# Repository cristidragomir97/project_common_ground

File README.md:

# Common Ground

Modular robot electronics built around a shared power and CAN backbone. Modules chain through XT30(2+2) connectors. Each module has a Seeed Studio XIAO RA4M1 for local control and is intended to communicate over a common CAN protocol.

## Shared architecture

- XT30(2+2) carries supply power, ground, CAN high, and CAN low.
- The XIAO RA4M1 and SN65HVD230 CAN transceiver provide local control and bus access.
- Boards include jumper-selectable 120 Ω CAN termination. Enable termination only at the two physical ends of a bus.

## Boards

| Board | Render | Role and hardware |
| --- | --- | --- |
| [mod_base](mod_base/) |  | - Battery input via XT60; charger/dock input via screw terminal<br>- Individually fused XT30(2+2) power/CAN outputs<br>- INA3221 monitors battery, dock, and load current<br>- UART and RS-485 interfaces |
| [mod_ddsm](mod_ddsm/) |  | - Four hub motor power outputs<br>- Four RS-485 and four UART connections, labelled FL/FR/BL/BR<br>- SP3485, TMUX1308 receive multiplexer, INA226 current monitor, and MOSFET power cutoff<br>- Two XT30(2+2) backbone connectors |
| [mod_feetech](mod_feetech/) |  | - Six three-pin Feetech servo connectors on a shared half-duplex data bus<br>- 8 A servo supply regulator (TPS56A37)<br>- Transmit/receive buffers, INA226 current monitor, and MOSFET power cutoff<br>- Two XT30(2+2) backbone connectors |
| [mod_sense](mod_sense/) |  | - LSM6DSOX six-axis IMU and MMC5983MA magnetometer over I²C<br>- Sensor interrupt signals<br>- Two XT30(2+2) backbone connectors |
| [mod_kitchensink](mod_kitchensink/mod_kitchensink/) |  | - Arduino-style power, digital/PWM, and analog headers<br>- Level shifters for compatibility with virtually every Arduino shield |
| [mod_raw](mod_raw/) | — | - Minimal starting point for custom modules<br>- Shared XIAO/CAN/power circuitry, INA226 current monitor, and MOSFET power cutoff |

## Example: XLeRobot module chain

The diagram shows one possible XLeRobot layout. The SBC receives power and connects to the control network through its own XT30(2+2) connection to the base board, then controls the robot modules. The Feetech boards locally drive their attached servos.

The base board provides six fused outputs, so these four modules use four separate outputs and leave two available. Each branch carries the same CAN bus, so connect only the two bus endpoints with termination enabled.

## Example: AMR with DDSM115 drive and RobStride arm

This AMR layout uses one mod_ddsm for four independently connected DDSM115 wheel motors, with the reBot Arm B601-DM and an IMU on separate base-board branches. The SBC connects through XT30(2+2) for power and control. The arm uses RobStride servos. Check the arm's connection and power requirements against its documentation before wiring.

The base outputs are drawn as separate branches for clarity. They remain electrically connected to the same power source and CAN network; the output fuses isolate branch faults, not CAN traffic. Check motor and arm peak currents against the battery, BMS, wiring, and branch fuse ratings.

## Repository

Each board directory contains KiCad project, schematic, and PCB layout files. Available board renders are shown above and collected in [renders](renders/).

This README describes the current hardware designs. A common CAN protocol is an intended system feature; firmware and a protocol specification are not currently included here.

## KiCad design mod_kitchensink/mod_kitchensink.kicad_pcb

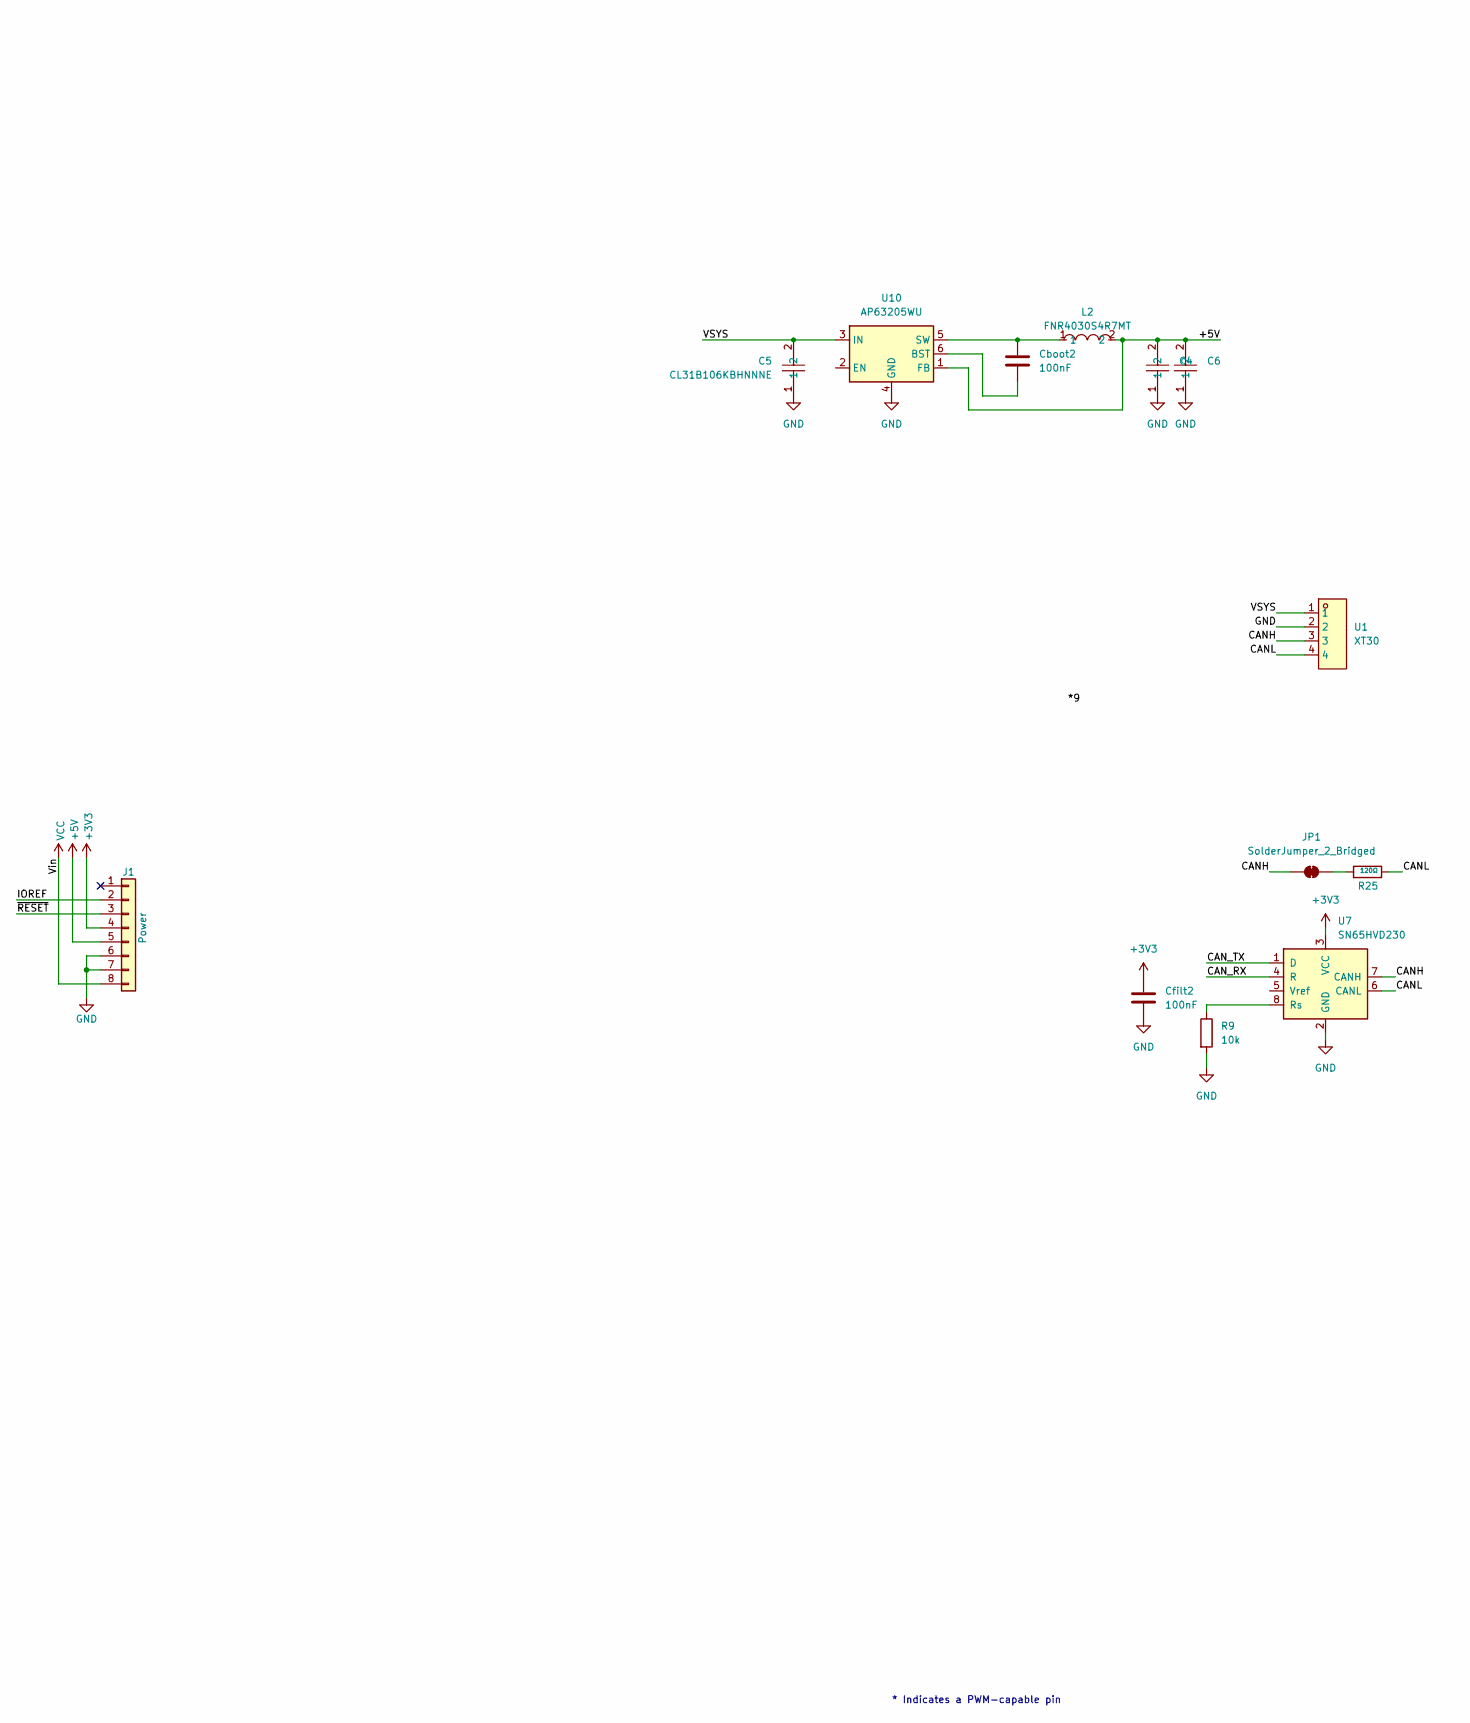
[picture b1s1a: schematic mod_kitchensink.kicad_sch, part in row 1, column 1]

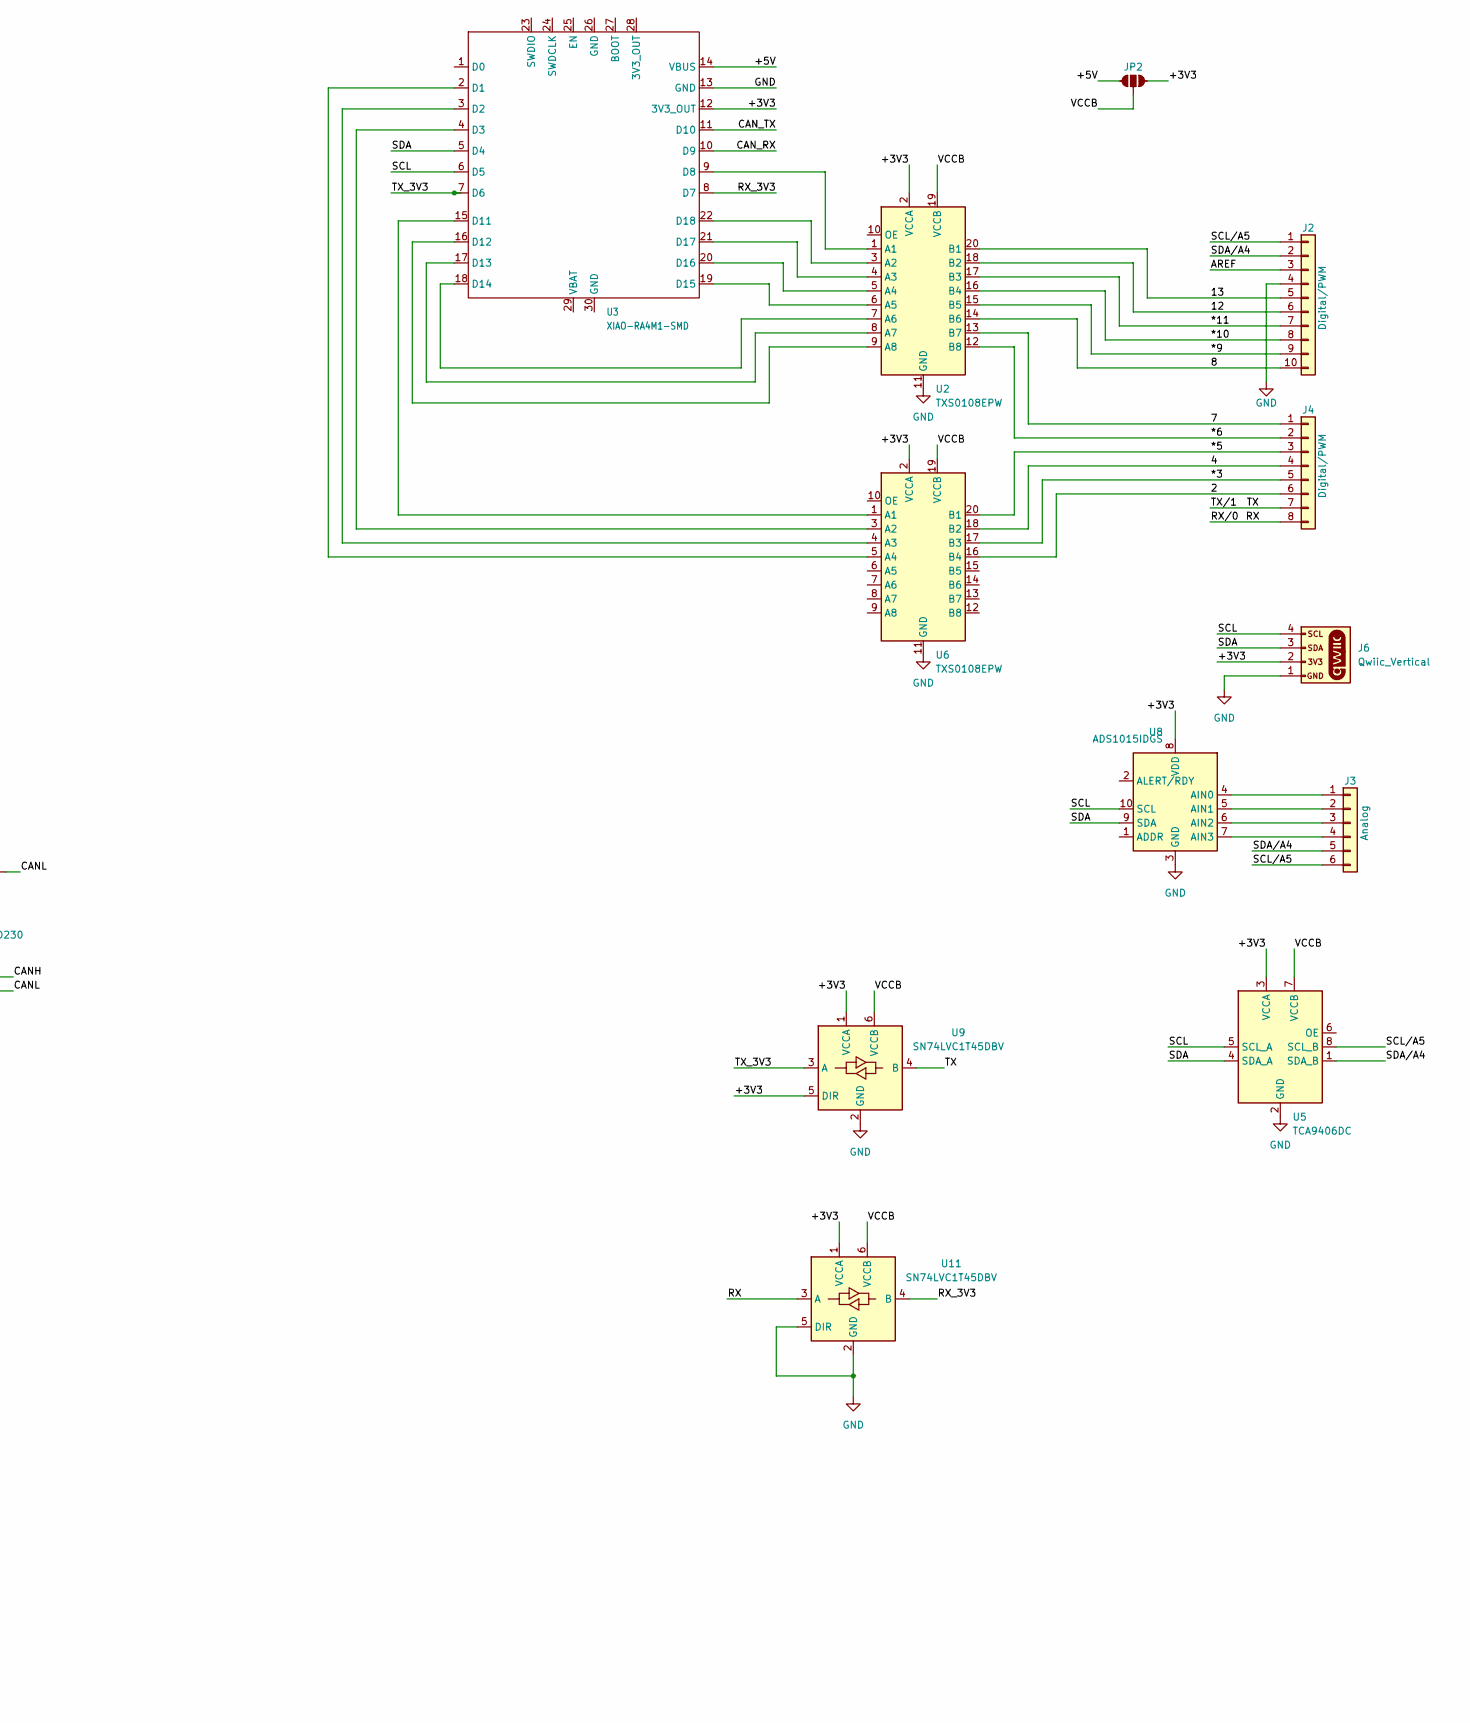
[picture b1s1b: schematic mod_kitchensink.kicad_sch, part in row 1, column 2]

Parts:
C4, C6: TCC0805X5R226M100FT; C0805; MPN TCC0805X5R226M100FT; LCSC Part C380338
C5: CL31B106KBHNNNE; C1206; MPN CL31B106KBHNNNE; LCSC Part C89632
Cboot2: 100nF; C_0603_1608Metric
Cfilt2: 100nF; C_0603_1608Metric
J1: Power; PinSocket_1x08_P2.54mm_Vertical
J2: Digital/PWM; PinSocket_1x10_P2.54mm_Vertical
J3: Analog; PinSocket_1x06_P2.54mm_Vertical
J4: Digital/PWM; PinSocket_1x08_P2.54mm_Vertical
J6: Qwiic_Vertical; JST_1x04_P1.0mm_Vertical_SMD
JP1: SolderJumper_2_Bridged; SolderJumper-2_P1.3mm_Bridged_Pad1.0x1.5mm
JP2: Jumper_3_NO_NoSilk
L2: FNR4030S4R7MT; IND-SMD_L4.0-W4.0_FNR40XXS; MPN FNR4030S4R7MT; LCSC Part C167874
R9: 10k; R_0402_1005Metric_Pad0.72x0.64mm_HandSolder
R25: 120Ω; R_0402_1005Metric; Overload Voltage (Max) 50V; Tolerance ±1%; Part 0402WGF1200TCE; LCSC C25079
U1: XT30; CONN-TH_4P-XT30PW-M; MPN XT30PW(2+2)-M.G.B; LCSC Part C19268030
U2, U6: TXS0108EPW; TSSOP-20_4.4x6.5mm_P0.65mm
U3: XIAO-RA4M1-SMD; XIAO-R4-SMD
U5: TCA9406DC
U7: SN65HVD230; SOIC-8_3.9x4.9mm_P1.27mm
U8: ADS1015IDGS; TSSOP-10_3x3mm_P0.5mm
U9, U11: SN74LVC1T45DBV; SOT-23-6
U10: AP63205WU; TSOT-23-6

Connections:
+3V3: Cfilt2.1, J1.4, J6.2, JP2.3 (C), U2.2 (VCCA), U3.12 (3V3_OUT), U5.3 (VCCA), U6.2 (VCCA), U7.3 (VCC), U8.8 (VDD), U9.1 (VCCA), U9.5 (DIR), U11.1 (VCCA)
+5V: C4.2, C6.2, J1.5, JP2.1 (A), L2.2, U3.14 (VBUS), U10.1 (FB)
/2: J4.6, U6.16 (B4)
/4: J4.4, U6.18 (B2)
/7: J4.1, U2.13 (B7)
/8: J2.10, U2.14 (B6)
/12: J2.6, U2.18 (B2)
/13: J2.5, U2.20 (B1)
/*3: J4.5, U6.17 (B3)
/*5: J4.3, U6.20 (B1)
/*6: J4.2, U2.12 (B8)
/*9: J2.9, U2.15 (B5)
/*10: J2.8, U2.16 (B4)
/*11: J2.7, U2.17 (B3)
/AREF: J2.3
/CANH: JP1.1 (A), U1.3, U7.7 (CANH)
/CANL: R25.2, U1.4, U7.6 (CANL)
/CAN_RX: U3.10 (D9), U7.4 (R)
/CAN_TX: U3.11 (D10), U7.1 (D)
/IOREF: J1.2
/RX: J4.8, U11.3 (A)
/RX_3V3: U3.8 (D7), U11.4 (B)
/SCL: J6.4, U3.6 (D5), U5.5 (SCL_A), U8.10 (SCL)
/SCL/A5: J2.1, J3.6, U5.8 (SCL_B)
/SDA: J6.3, U3.5 (D4), U5.4 (SDA_A), U8.9 (SDA)
/SDA/A4: J2.2, J3.5, U5.1 (SDA_B)
/TX: J4.7, U9.4 (B)
/TX_3V3: U3.7 (D6), U9.3 (A)
/VCCB: JP2.2 (B), U2.19 (VCCB), U5.7 (VCCB), U6.19 (VCCB), U9.6 (VCCB), U11.6 (VCCB)
/VSYS: C5.2, U1.1, U10.3 (IN)
/~RESET: J1.3
GND: C4.1, C5.1, C6.1, Cfilt2.2, J1.6, J1.7, J2.4, J6.1, R9.2, U1.2, U2.11 (GND), U3.13 (GND), U5.2 (GND), U6.11 (GND), U7.2 (GND), U8.3 (GND), U9.2 (GND), U10.4 (GND), U11.2 (GND), U11.5 (DIR)
unnamed: J3.1, U8.4 (AIN0)
unnamed: J3.2, U8.5 (AIN1)
unnamed: J3.3, U8.6 (AIN2)
unnamed: J3.4, U8.7 (AIN3)
unnamed: JP1.2 (B), R25.1
unnamed: U2.1 (A1), U3.9 (D8)
unnamed: U2.3 (A2), U3.22 (D18)
unnamed: U2.4 (A3), U3.21 (D17)
unnamed: U2.5 (A4), U3.20 (D16)
unnamed: U2.6 (A5), U3.19 (D15)
unnamed: U2.7 (A6), U3.18 (D14)
unnamed: U2.8 (A7), U3.17 (D13)
unnamed: U2.9 (A8), U3.16 (D12)
unnamed: U3.2 (D1), U6.5 (A4)
unnamed: U3.3 (D2), U6.4 (A3)
unnamed: U3.4 (D3), U6.3 (A2)
unnamed: U3.15 (D11), U6.1 (A1)
unnamed: R9.1, U7.8 (Rs)
unnamed: Cboot2.2, U10.6 (BST)
unnamed: Cboot2.1, L2.1, U10.5 (SW)
VCC: J1.8

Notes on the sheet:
* Indicates a PWM-capable pin

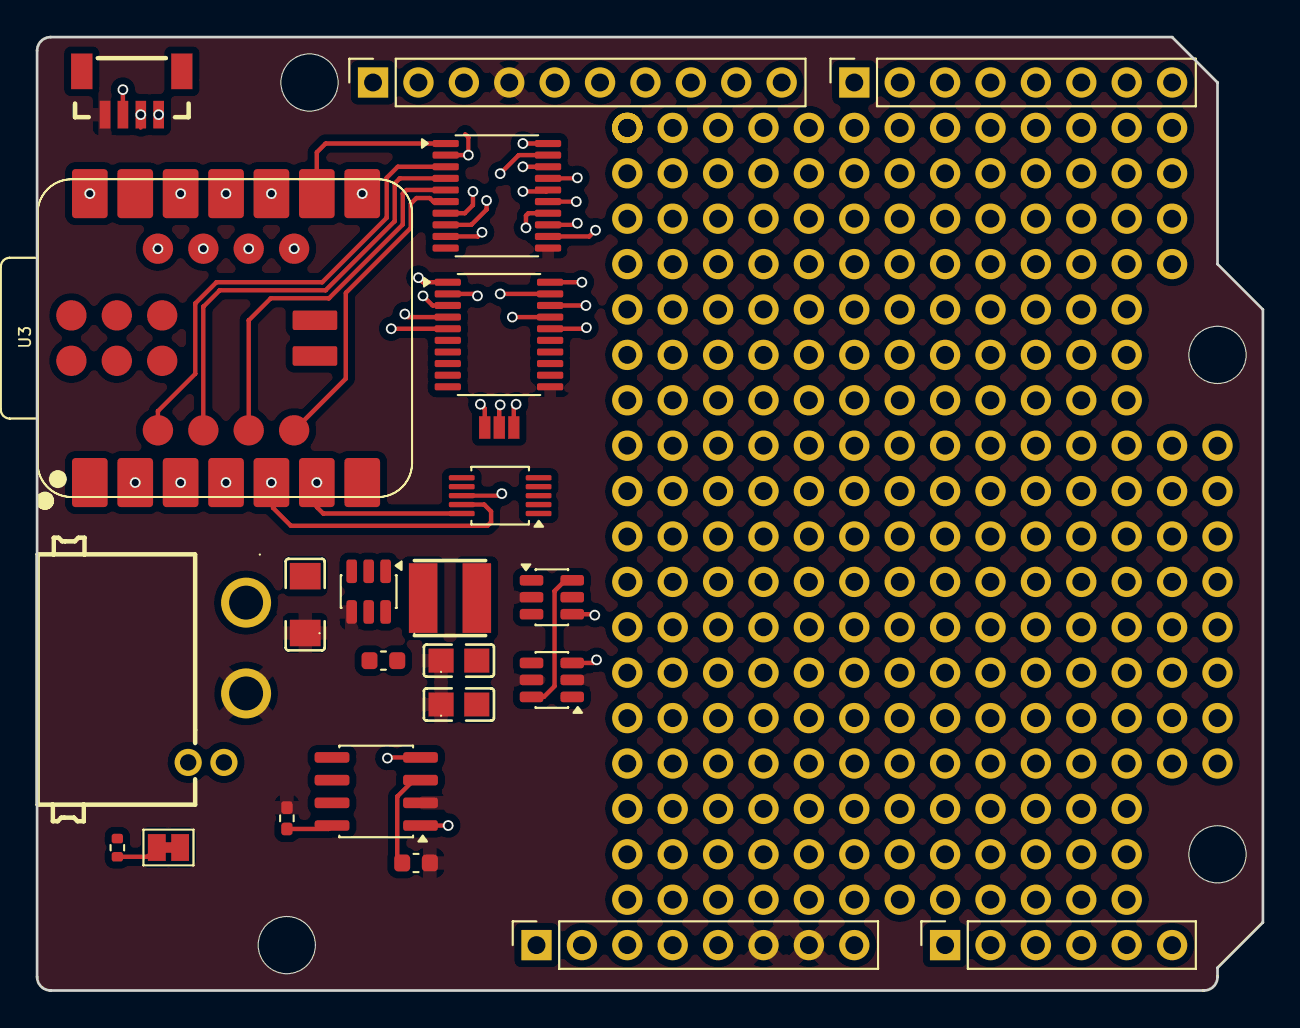
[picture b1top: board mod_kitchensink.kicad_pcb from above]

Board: 4 copper layers, 68.6 x 53.3 mm, 264 parts (0 on the bottom side), 49 nets.

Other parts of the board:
H6, H7, H8, H9, H10, H11, H12, H13, H14, H15, H16, H17, H18, H19, H20, H21, H22, H23, H24, H25, H26, H27, H28, H29, H30, H31, H32, H33, H34, H35, H36, H37, H38, H39, H40, H41, H42, H43, H44, H45, H46, H47, H48, H49, H50, H51, H52, H53, H54, H55, H56, H57, H58, H59, H60, H61, H62, H63, H64, H65, H66, H67, H68, H69, H74, H75, H76, H77, H78, H79, H80, H81, H82, H83, H84, H85, H90, H91, H92, H93, H94, H95, H96, H97, H98, H99, H100, H101, H106, H107, H108, H109, H110, H111, H112, H113, H114, H115, H116, H117, H118, H119, H124, H125, H126, H127, H128, H129, H130, H131, H132, H133, H134, H135, H136, H137, H140, H141, H142, H143, H144, H145, H146, H147, H148, H149, H150, H151, H152, H153, H156, H157, H158, H159, H160, H161, H162, H163, H164, H165, H166, H167, H168, H169, H172, H173, H174, H175, H176, H177, H178, H179, H180, H181, H182, H183, H184, H185, H188, H189, H190, H191, H192, H193, H194, H195, H196, H197, H198, H199, H200, H201, H206, H207, H208, H209, H210, H211, H212, H213, H214, H215, H216, H217, H218, H219, H223, H224, H225, H226, H227, H228, H229, H230, H231, H232, H233, H234, H235, H236, H240, H241, H242, H243, H244, H245, H246, H247, H248, H249, H250, H251, H256, H257, H258, H259, H260, H261, H262, H263, H264, H265, H266, H267, H278, H279, H280, H281, H282, H283, H284, H285, H286, H287, H288, H289: Perf_1x01_Square
MH1, MH2, MH3, MH4: MountingHole_3.2mm

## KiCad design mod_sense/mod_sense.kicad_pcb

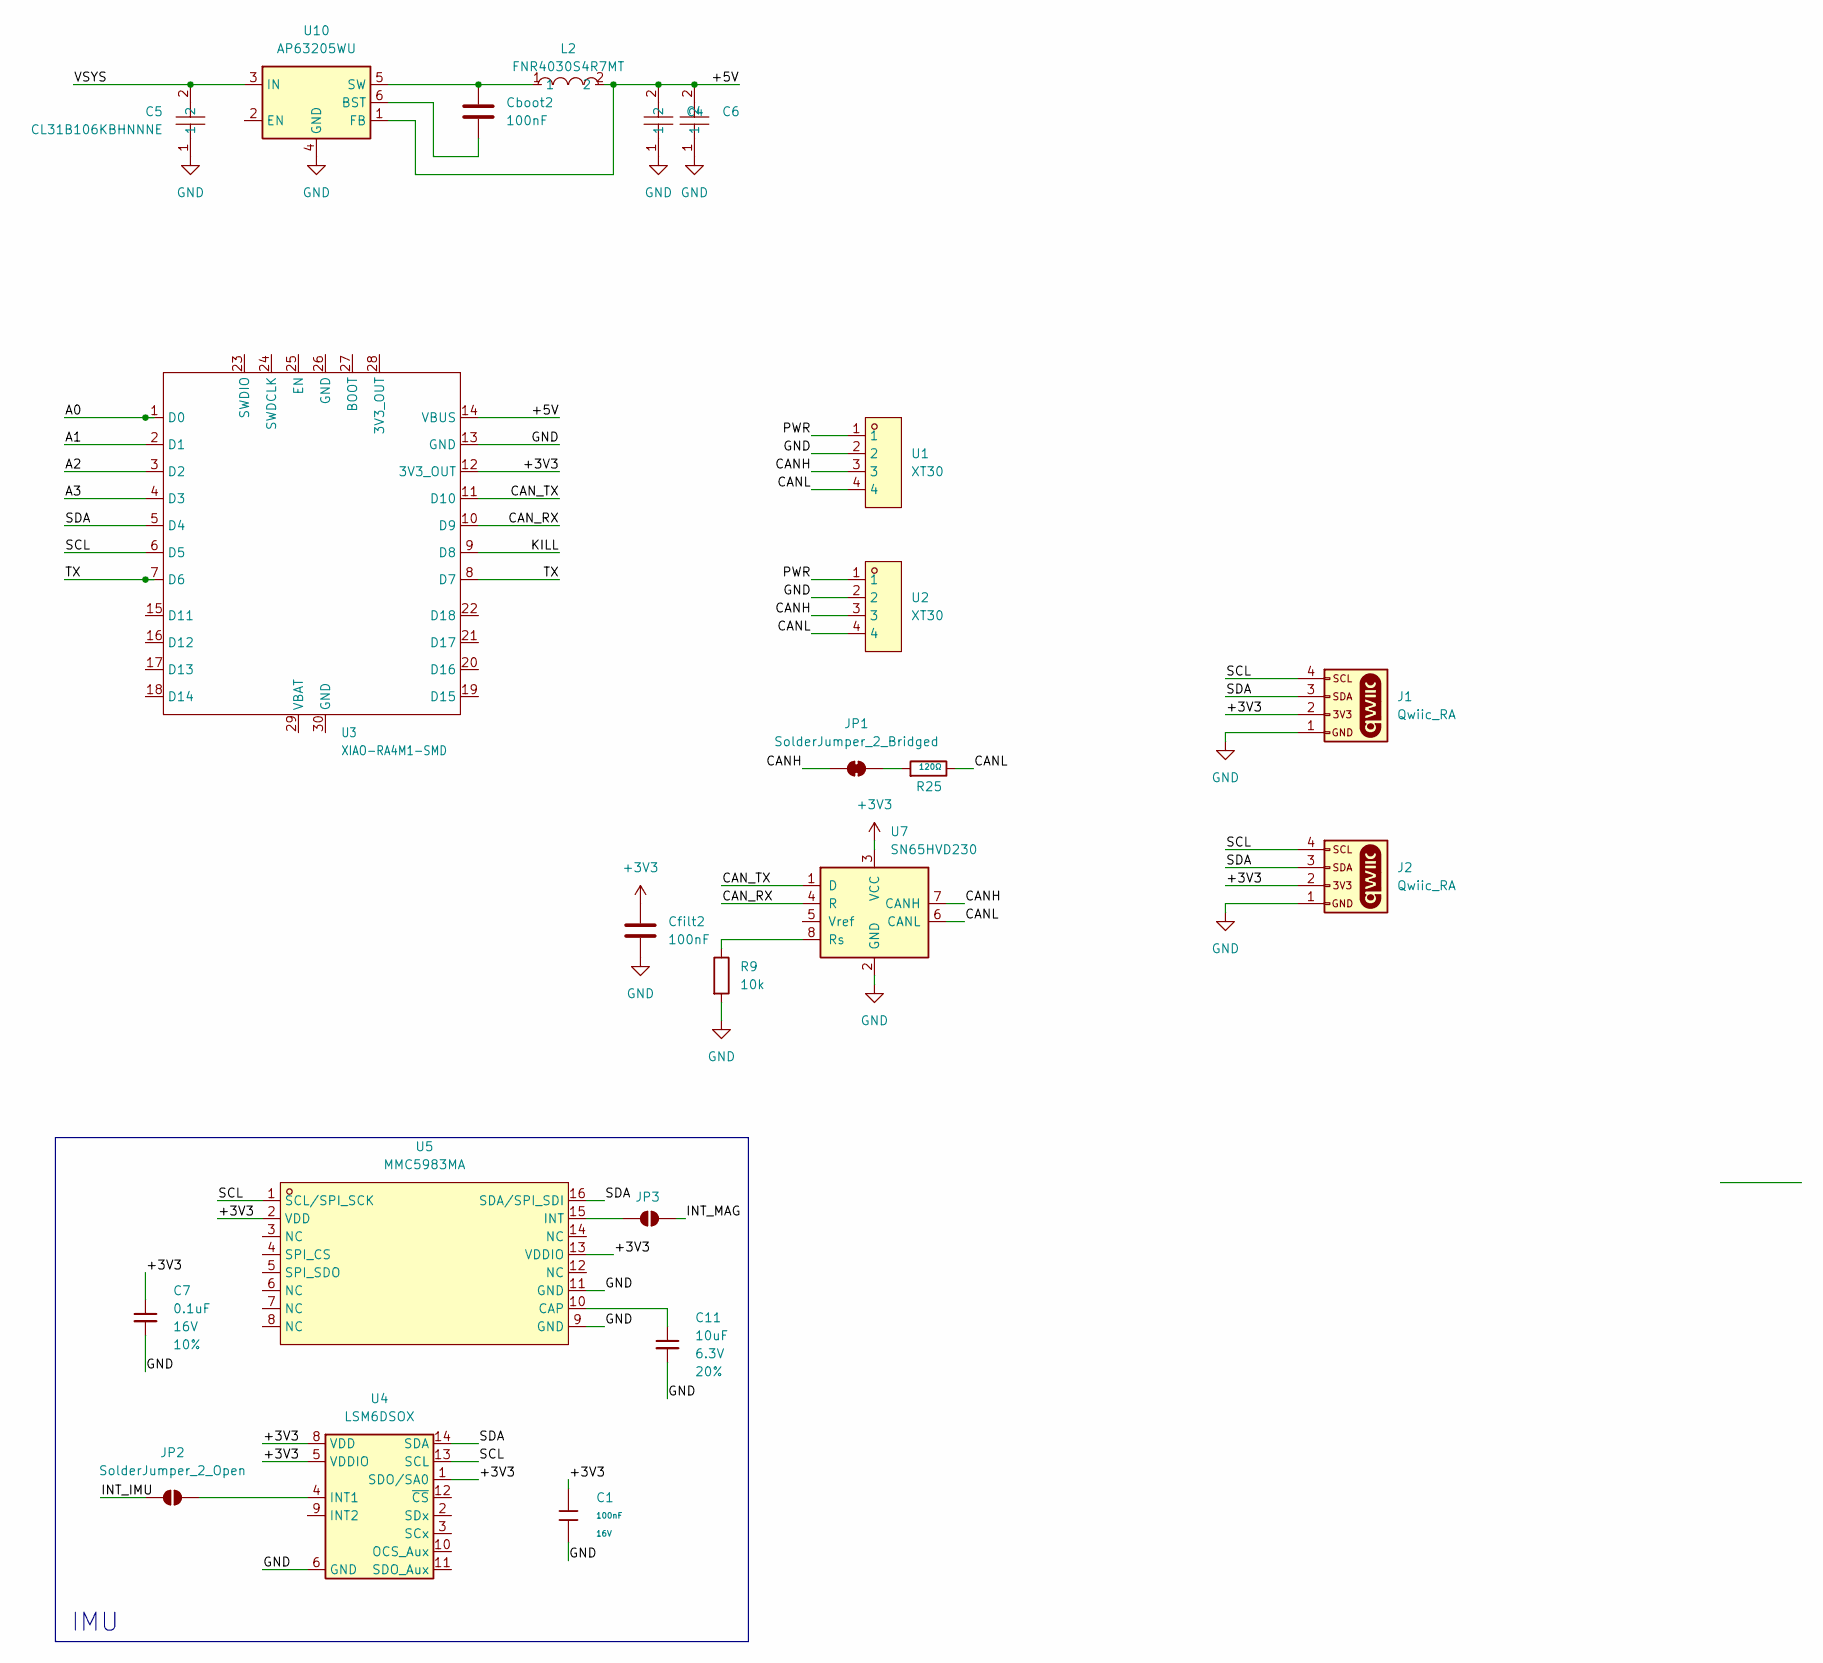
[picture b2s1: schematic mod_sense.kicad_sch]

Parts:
C1: 100nF; C_0402; Voltage Rated 16V; Tolerance ±10%; Part CL05B104KO5NNNC; LCSC C1525
C4, C6: TCC0805X5R226M100FT; C0805; MPN TCC0805X5R226M100FT; LCSC Part C380338
C5: CL31B106KBHNNNE; C1206; MPN CL31B106KBHNNNE; LCSC Part C89632
C7: 0.1uF; C_0402_1005Metric; Voltage 16V; Tolerance 10%
C11: 10uF; C_0402_1005Metric; Voltage 6.3V; Tolerance 20%
Cboot2: 100nF; C_0603_1608Metric
Cfilt2: 100nF; C_0603_1608Metric
J1, J2: Qwiic_RA; JST_1x04_P1.0mm_Horizontal_SMD
JP1: SolderJumper_2_Bridged; SolderJumper-2_P1.3mm_Bridged_Pad1.0x1.5mm
JP2, JP3: SolderJumper_2_Open; SolderJumper-2_P1.3mm_Open_RoundedPad1.0x1.5mm
L2: FNR4030S4R7MT; IND-SMD_L4.0-W4.0_FNR40XXS; MPN FNR4030S4R7MT; LCSC Part C167874
R9: 10k; R_0402_1005Metric_Pad0.72x0.64mm_HandSolder
R25: 120Ω; R_0402_1005Metric; Overload Voltage (Max) 50V; Tolerance ±1%; Part 0402WGF1200TCE; LCSC C25079
U1, U2: XT30; CONN-TH_4P-XT30PW-M; MPN XT30PW(2+2)-M.G.B; LCSC Part C19268030
U3: XIAO-RA4M1-SMD; XIAO-R4-SMD
U4: LSM6DSOX; ST_LGA-14L_2.5x3.0mm_P0.5mm_4x3
U5: MMC5983MA; LGA-16_L3.0-W3.0-P0.50-BL_SQ; LCSC Part C404329
U7: SN65HVD230; SOIC-8_3.9x4.9mm_P1.27mm
U10: AP63205WU; TSOT-23-6

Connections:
+3V3: C1.1, C7.1, Cfilt2.1, J1.2, J2.2, U3.12 (3V3_OUT), U4.1 (SDO/SA0), U4.5 (VDDIO), U4.8 (VDD), U5.2 (VDD), U5.13 (VDDIO), U7.3 (VCC)
/+5V: C4.2, C6.2, L2.2, U3.14 (VBUS), U10.1 (FB)
/A0: U3.1 (D0)
/A1: U3.2 (D1)
/A2: U3.3 (D2)
/A3: U3.4 (D3)
/CANH: JP1.1 (A), U1.3, U2.3, U7.7 (CANH)
/CANL: R25.2, U1.4, U2.4, U7.6 (CANL)
/CAN_RX: U3.10 (D9), U7.4 (R)
/CAN_TX: U3.11 (D10), U7.1 (D)
/INT_IMU: JP2.1 (A)
/INT_MAG: JP3.2 (B)
/KILL: U3.9 (D8)
/PWR: U1.1, U2.1
/SCL: J1.4, J2.4, U3.6 (D5), U4.13 (SCL), U5.1 (SCL/SPI_SCK)
/SDA: J1.3, J2.3, U3.5 (D4), U4.14 (SDA), U5.16 (SDA/SPI_SDI)
/TX: U3.7 (D6), U3.8 (D7)
/VSYS: C5.2, U10.3 (IN)
GND: C1.2, C4.1, C5.1, C6.1, C7.2, C11.2, Cfilt2.2, J1.1, J2.1, R9.2, U1.2, U2.2, U3.13 (GND), U4.6 (GND), U4.7 (GND), U5.9 (GND), U5.11 (GND), U7.2 (GND), U10.4 (GND)
unnamed: JP1.2 (B), R25.1
unnamed: JP2.2 (B), U4.4 (INT1)
unnamed: JP3.1 (A), U5.15 (INT)
unnamed: C11.1, U5.10 (CAP)
unnamed: R9.1, U7.8 (Rs)
unnamed: Cboot2.2, U10.6 (BST)
unnamed: Cboot2.1, L2.1, U10.5 (SW)

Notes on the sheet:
IMU

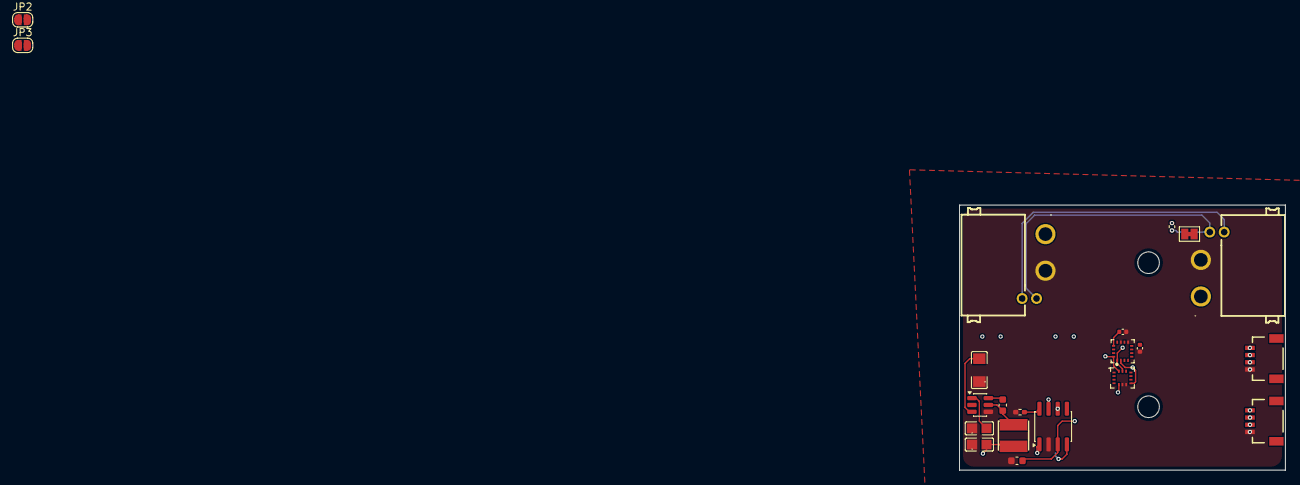
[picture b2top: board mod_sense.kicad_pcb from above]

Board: 4 copper layers, 45.2 x 36.8 mm, 22 parts (1 on the bottom side), 19 nets.

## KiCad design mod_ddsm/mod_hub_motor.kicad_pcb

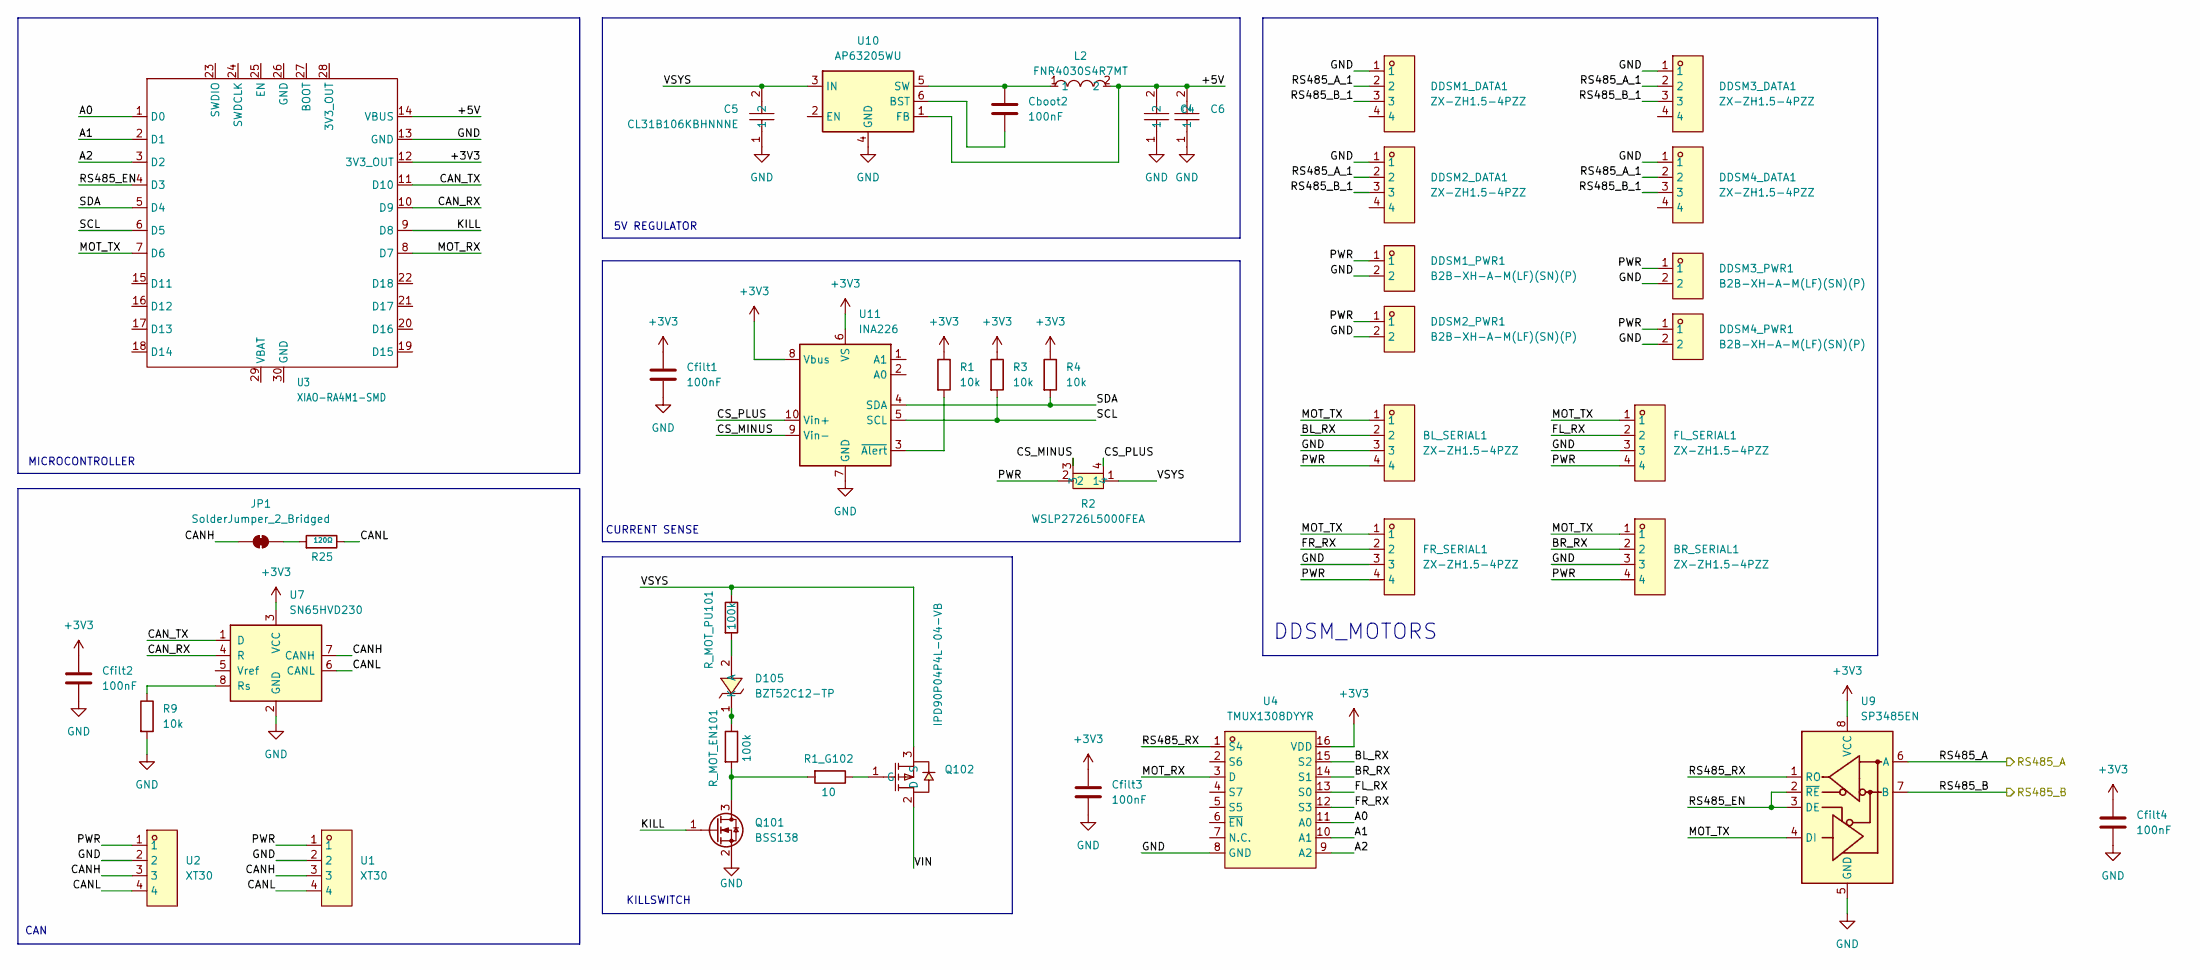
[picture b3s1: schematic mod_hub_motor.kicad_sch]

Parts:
BL_SERIAL1: ZX-ZH1.5-4PZZ; CONN-TH_4P-P1.50_A1501-WV04; LCSC Part C46533521
BR_SERIAL1: ZX-ZH1.5-4PZZ; CONN-TH_4P-P1.50_A1501-WV04; LCSC Part C46533521
C4, C6: TCC0805X5R226M100FT; C0805; MPN TCC0805X5R226M100FT; LCSC Part C380338
C5: CL31B106KBHNNNE; C1206; MPN CL31B106KBHNNNE; LCSC Part C89632
Cboot2: 100nF; C_0603_1608Metric
Cfilt1, Cfilt2, Cfilt3, Cfilt4: 100nF; C_0603_1608Metric
D105: BZT52C12-TP; SOD-123_L2.7-W1.6-LS3.7-RD-A; MPN BZT52C12-TP; LCSC Part C668891
DDSM1_DATA1, DDSM2_DATA1, DDSM3_DATA1, DDSM4_DATA1: ZX-ZH1.5-4PZZ; CONN-TH_4P-P1.50_A1501-WV04; LCSC Part C46533521
DDSM1_PWR1, DDSM2_PWR1, DDSM3_PWR1, DDSM4_PWR1: B2B-XH-A-M(LF)(SN)(P); CONN-TH_2P-P2.50_JST_B2B-XH-A-M; LCSC Part C5118732
FL_SERIAL1: ZX-ZH1.5-4PZZ; CONN-TH_4P-P1.50_A1501-WV04; LCSC Part C46533521
FR_SERIAL1: ZX-ZH1.5-4PZZ; CONN-TH_4P-P1.50_A1501-WV04; LCSC Part C46533521
JP1: SolderJumper_2_Bridged; SolderJumper-2_P1.3mm_Bridged_Pad1.0x1.5mm
L2: FNR4030S4R7MT; IND-SMD_L4.0-W4.0_FNR40XXS; MPN FNR4030S4R7MT; LCSC Part C167874
Q101: BSS138; SOT-23
Q102: IPD90P04P4L-04-VB; TO-252-2_L6.6-W6.1-P4.57-LS9.9-BR-CW; MPN IPD90P04P4L-04-VB; LCSC Part C7429006
R1, R3, R4, R9: 10k; R_0402_1005Metric_Pad0.72x0.64mm_HandSolder
R1_G102: 10; R_0402_1005Metric
R2: WSLP2726L5000FEA; RES-SMD_4P-L6.9-W6.6_WSLP2726L5000FEA; LCSC Part C844297
R25: 120Ω; R_0402; Overload Voltage (Max) 50V; Tolerance ±1%; Part 0402WGF1200TCE; LCSC C25079
R_MOT_EN101: 100k; R_0402_1005Metric
R_MOT_PU101: 100k; R_0402_1005Metric
U1, U2: XT30; CONN-TH_4P-XT30PW-M; MPN XT30PW(2+2)-M.G.B; LCSC Part C19268030
U3: XIAO-RA4M1-SMD; XIAO-R4-SMD
U4: TMUX1308DYYR; SOT-23-THN-16_L4.0-W2.0-P0.50-LS3.3-BL; MPN TMUX1308DYYR; LCSC Part C2877584
U7: SN65HVD230; SOIC-8_3.9x4.9mm_P1.27mm
U9: SP3485EN; SOIC-8_3.9x4.9mm_P1.27mm
U10: AP63205WU; TSOT-23-6
U11: INA226; TSSOP-10_3x3mm_P0.5mm

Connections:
+3V3: Cfilt1.1, Cfilt2.1, Cfilt3.1, Cfilt4.1, R1.1, R3.1, R4.1, U3.12 (3V3_OUT), U4.16 (VDD), U7.3 (VCC), U9.8 (VCC), U11.6 (VS), U11.8 (Vbus)
/+5V: C4.2, C6.2, L2.2, U3.14 (VBUS), U10.1 (FB)
/A0: U3.1 (D0), U4.11 (A0)
/A1: U3.2 (D1), U4.10 (A1)
/A2: U3.3 (D2), U4.9 (A2)
/BL_RX: BL_SERIAL1.2, U4.15 (S2)
/BR_RX: BR_SERIAL1.2, U4.14 (S1)
/CANH: JP1.1 (A), U1.3, U2.3, U7.7 (CANH)
/CANL: R25.2, U1.4, U2.4, U7.6 (CANL)
/CAN_RX: U3.10 (D9), U7.4 (R)
/CAN_TX: U3.11 (D10), U7.1 (D)
/CS_MINUS: R2.3, U11.9 (Vin-)
/CS_PLUS: R2.4, U11.10 (Vin+)
/FL_RX: FL_SERIAL1.2, U4.13 (S0)
/FR_RX: FR_SERIAL1.2, U4.12 (S3)
/KILL: Q101.1 (G), U3.9 (D8)
/MOT_RX: U3.8 (D7), U4.3 (D)
/MOT_TX: BL_SERIAL1.1, BR_SERIAL1.1, FL_SERIAL1.1, FR_SERIAL1.1, U3.7 (D6), U9.4 (DI)
/PWR: BL_SERIAL1.4, BR_SERIAL1.4, DDSM1_PWR1.1, DDSM2_PWR1.1, DDSM3_PWR1.1, DDSM4_PWR1.1, FL_SERIAL1.4, FR_SERIAL1.4, R2.2, U1.1, U2.1
/RS485_A: U9.6 (A)
/RS485_A_1: DDSM1_DATA1.2, DDSM2_DATA1.2, DDSM3_DATA1.2, DDSM4_DATA1.2
/RS485_B: U9.7 (B)
/RS485_B_1: DDSM1_DATA1.3, DDSM2_DATA1.3, DDSM3_DATA1.3, DDSM4_DATA1.3
/RS485_EN: U3.4 (D3), U9.2 (~RE), U9.3 (DE)
/RS485_RX: U4.1 (S4), U9.1 (RO)
/SCL: R3.2, U3.6 (D5), U11.5 (SCL)
/SDA: R4.2, U3.5 (D4), U11.4 (SDA)
/VIN: Q102.2 (D)
/VSYS: C5.2, Q102.3 (S), R2.1, R_MOT_PU101.1, U10.3 (IN)
GND: BL_SERIAL1.3, BR_SERIAL1.3, C4.1, C5.1, C6.1, Cfilt1.2, Cfilt2.2, Cfilt3.2, Cfilt4.2, DDSM1_DATA1.1, DDSM1_PWR1.2, DDSM2_DATA1.1, DDSM2_PWR1.2, DDSM3_DATA1.1, DDSM3_PWR1.2, DDSM4_DATA1.1, DDSM4_PWR1.2, FL_SERIAL1.3, FR_SERIAL1.3, Q101.2 (S), R9.2, U1.2, U2.2, U3.13 (GND), U4.8 (GND), U7.2 (GND), U9.5 (GND), U10.4 (GND), U11.7 (GND)
unnamed: D105.2 (A), R_MOT_PU101.2
unnamed: D105.1 (K), R_MOT_EN101.1
unnamed: JP1.2 (B), R25.1
unnamed: Q101.3 (D), R1_G102.2, R_MOT_EN101.2
unnamed: Q102.1 (G), R1_G102.1
unnamed: R9.1, U7.8 (Rs)
unnamed: Cboot2.2, U10.6 (BST)
unnamed: Cboot2.1, L2.1, U10.5 (SW)
unnamed: R1.2, U11.3 (~Alert)

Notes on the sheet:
DDSM_MOTORS
5V REGULATOR
MICROCONTROLLER
CURRENT SENSE
KILLSWITCH
CAN

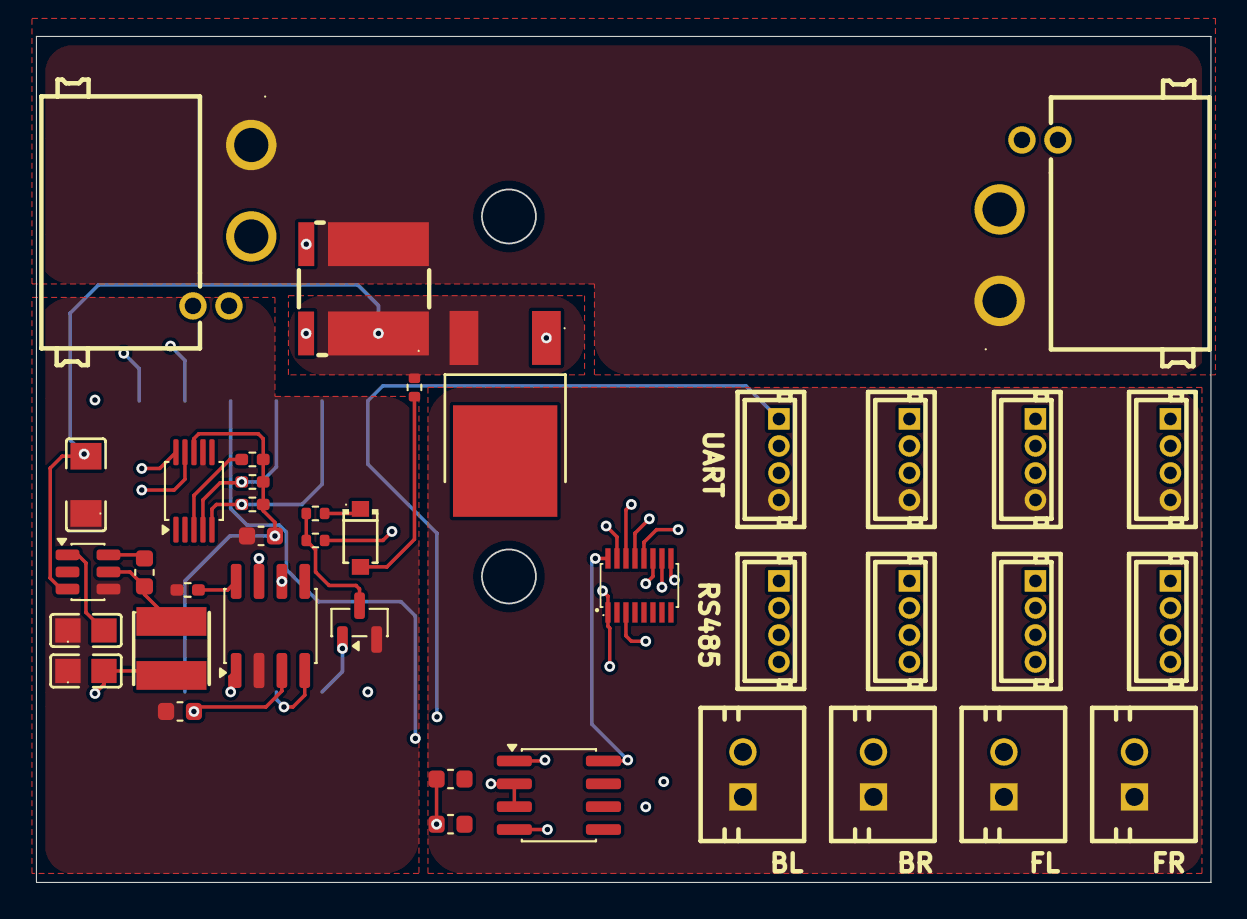
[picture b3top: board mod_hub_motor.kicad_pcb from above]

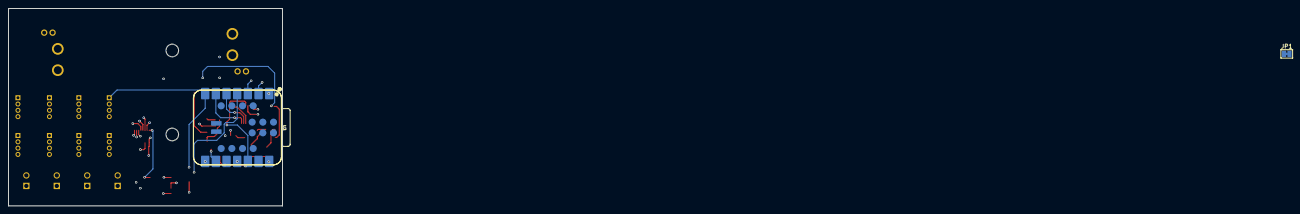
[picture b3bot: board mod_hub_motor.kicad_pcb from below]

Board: 4 copper layers, 65.2 x 47.0 mm, 41 parts (2 on the bottom side), 35 nets.
